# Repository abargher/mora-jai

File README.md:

# Project Mora Jai

A physical Mora Jai puzzle box (from Blue Prince) with programmable RGB LEDs.

Hardware is licensed under the `CERN-OHL-S-2.0` license (e.g., files in`pcb/`).

Code is licensed under the `GPL-3.0-or-later` license.

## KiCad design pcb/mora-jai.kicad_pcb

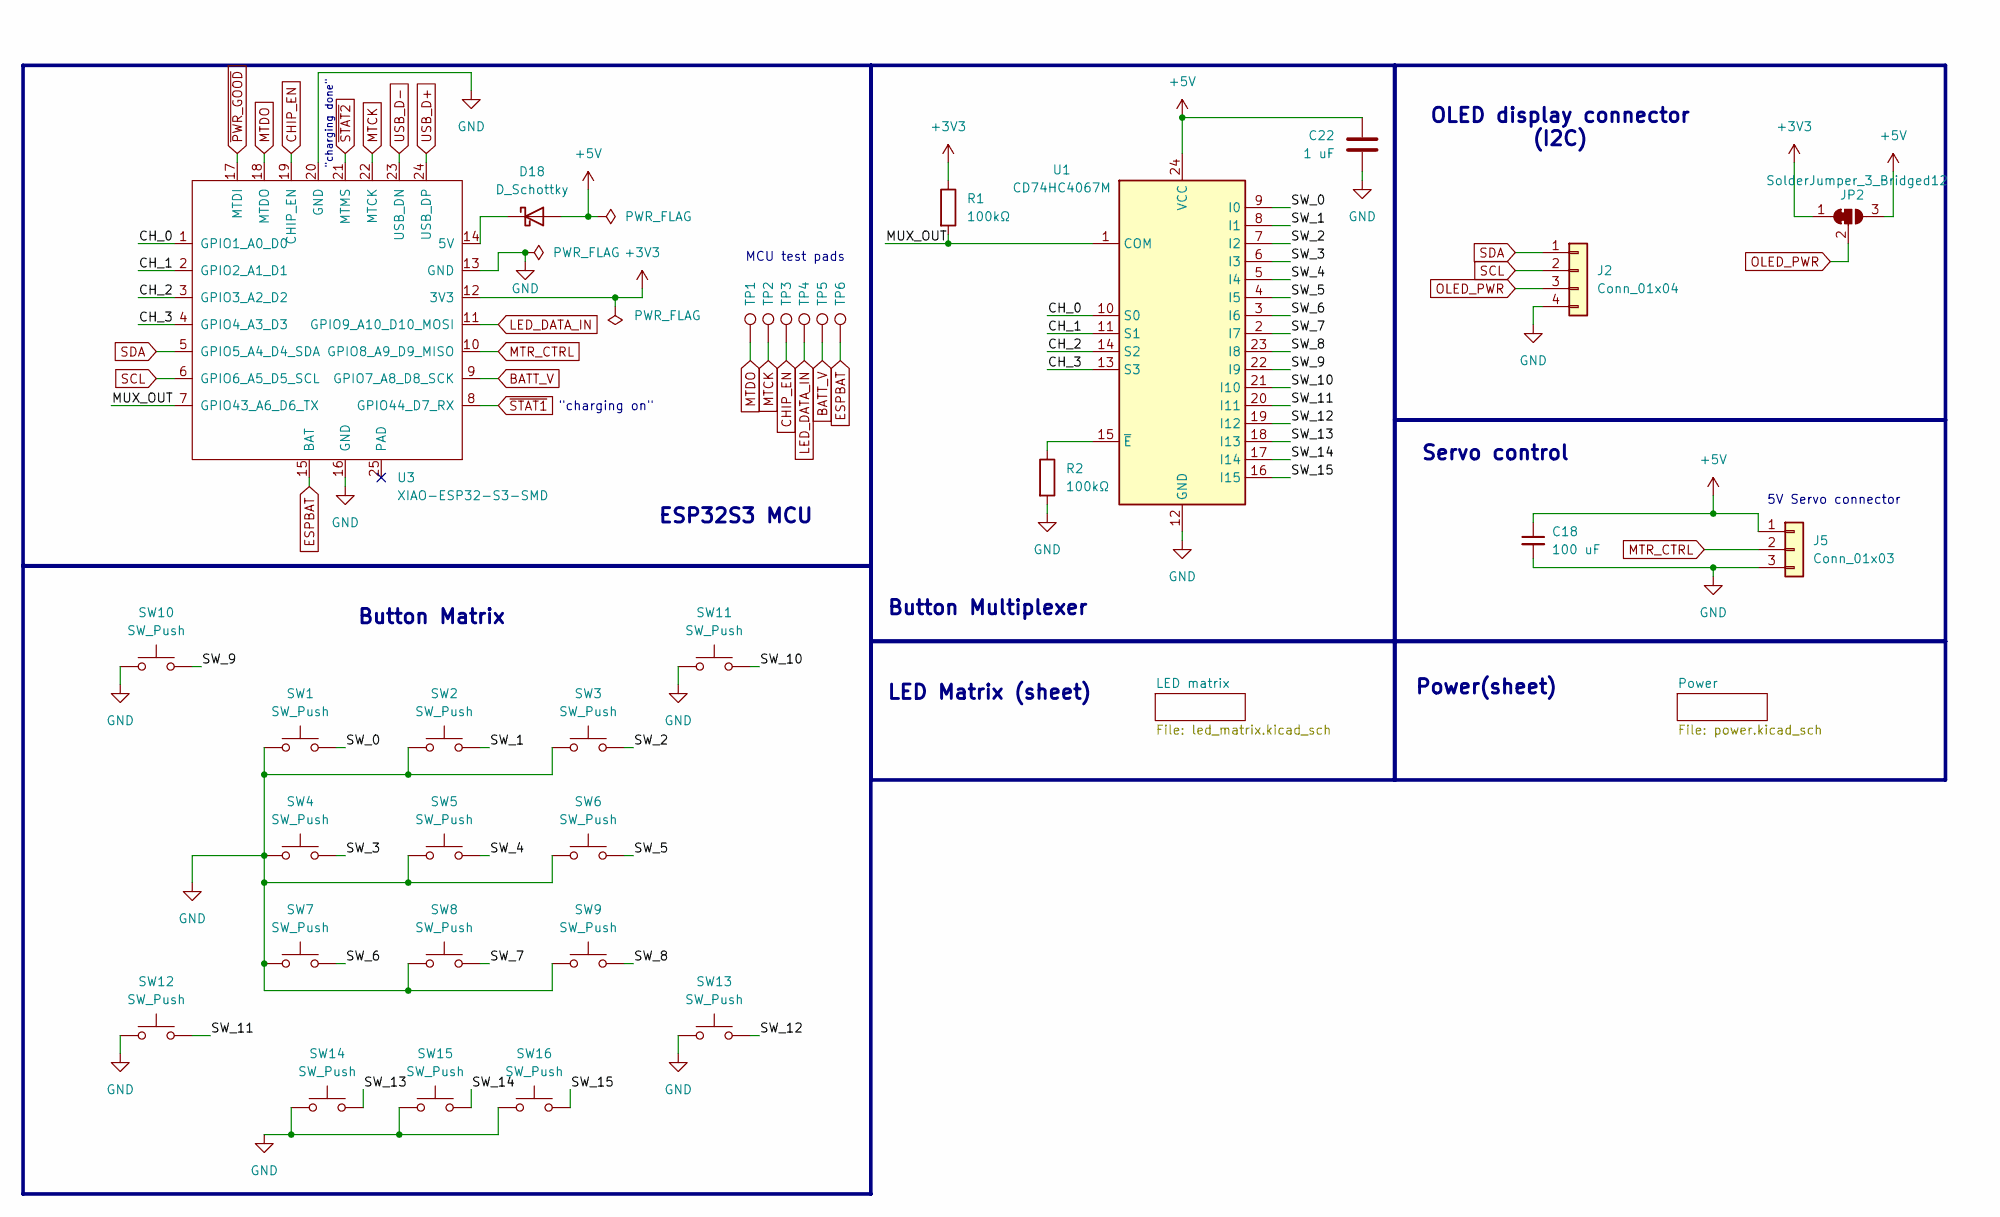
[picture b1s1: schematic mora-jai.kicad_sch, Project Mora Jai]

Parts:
C18: 100 uF; C_0805_2012Metric_Pad1.18x1.45mm_HandSolder
C22: 1 uF; C_0805_2012Metric_Pad1.18x1.45mm_HandSolder
D18: D_Schottky; D_SOD-123F
J2: Conn_01x04; PinSocket_1x04_P2.54mm_Vertical
J5: Conn_01x03; PinHeader_1x03_P2.54mm_Vertical
JP2: SolderJumper_3_Bridged12; SolderJumper-3_P1.3mm_Bridged12_RoundedPad1.0x1.5mm
R1, R2: 100kΩ; R_0805_2012Metric_Pad1.20x1.40mm_HandSolder
SW1, SW2, SW3, SW4, SW5, SW6, SW7, SW8, SW9, SW10, SW11, SW12, SW13, SW14, SW15, SW16: SW_Push; SW_PUSH_6mm_H5mm
TP1, TP2, TP3, TP4, TP5, TP6: TestPoint; TestPoint_Pad_D2.5mm
U1: CD74HC4067M; SOIC-24W_7.5x15.4mm_P1.27mm
U3: XIAO-ESP32-S3-SMD; XIAO-ESP32S3-SMD-batt-tht

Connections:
+3V3: JP2.1 (A), R1.1, U3.12 (3V3); also elsewhere on the board
+5V: C18.1, C22.2, D18.2 (A), J5.1, JP2.3 (B), U1.24 (VCC); also elsewhere on the board
/CH_0: U1.10 (S0), U3.1 (GPIO1_A0_D0)
/CH_1: U1.11 (S1), U3.2 (GPIO2_A1_D1)
/CH_2: U1.14 (S2), U3.3 (GPIO3_A2_D2)
/CH_3: U1.13 (S3), U3.4 (GPIO4_A3_D3)
/MUX_OUT: R1.2, U1.1 (COM), U3.7 (GPIO43_A6_D6_TX)
/SW_0: SW1.2, U1.9 (I0)
/SW_1: SW2.2, U1.8 (I1)
/SW_2: SW3.2, U1.7 (I2)
/SW_3: SW4.2, U1.6 (I3)
/SW_4: SW5.2, U1.5 (I4)
/SW_5: SW6.2, U1.4 (I5)
/SW_6: SW7.2, U1.3 (I6)
/SW_7: SW8.2, U1.2 (I7)
/SW_8: SW9.2, U1.23 (I8)
/SW_9: SW10.2, U1.22 (I9)
/SW_10: SW11.2, U1.21 (I10)
/SW_11: SW12.2, U1.20 (I11)
/SW_12: SW13.2, U1.19 (I12)
/SW_13: SW14.2, U1.18 (I13)
/SW_14: SW15.2, U1.17 (I14)
/SW_15: SW16.2, U1.16 (I15)
BATT_V: TP5.1 (1_1), U3.9 (GPIO7_A8_D8_SCK); also elsewhere on the board
CHIP_EN: TP3.1 (1_1), U3.19 (CHIP_EN)
ESPBAT: TP6.1 (1_1), U3.15 (BAT)
GND: C18.2, C22.1, J2.4, J5.3, R2.2, SW1.1, SW2.1, SW3.1, SW4.1, SW5.1, SW6.1, SW7.1, SW8.1, SW9.1, SW10.1, SW11.1, SW12.1, SW13.1, SW14.1, SW15.1, SW16.1, U1.12 (GND), U3.13 (GND), U3.16 (GND), U3.20 (GND); also elsewhere on the board
LED_DATA_IN: TP4.1 (1_1), U3.11 (GPIO9_A10_D10_MOSI); also elsewhere on the board
MTCK: TP2.1 (1_1), U3.22 (MTCK)
MTDO: TP1.1 (1_1), U3.18 (MTDO)
MTR_CTRL: J5.2, U3.10 (GPIO8_A9_D9_MISO)
unnamed: D18.1 (K), U3.14 (5V)
unnamed: R2.1, U1.15 (~E)
OLED_PWR: J2.3, JP2.2 (C)
SCL: J2.2, U3.6 (GPIO6_A5_D5_SCL)
SDA: J2.1, U3.5 (GPIO5_A4_D4_SDA)
USB_D+: U3.24 (USB_DP); also elsewhere on the board
USB_D-: U3.23 (USB_DN); also elsewhere on the board
~PWR_GOOD: U3.17 (MTDI); also elsewhere on the board
~STAT1: U3.8 (GPIO44_D7_RX); also elsewhere on the board
~STAT2: U3.21 (MTMS); also elsewhere on the board

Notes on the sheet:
Power(sheet)
ESP32S3 MCU
Servo control
"charging on"
"charging done"
MCU test pads
5V Servo connector
Button Matrix
OLED display connector (I2C)
LED Matrix (sheet)
Button Multiplexer

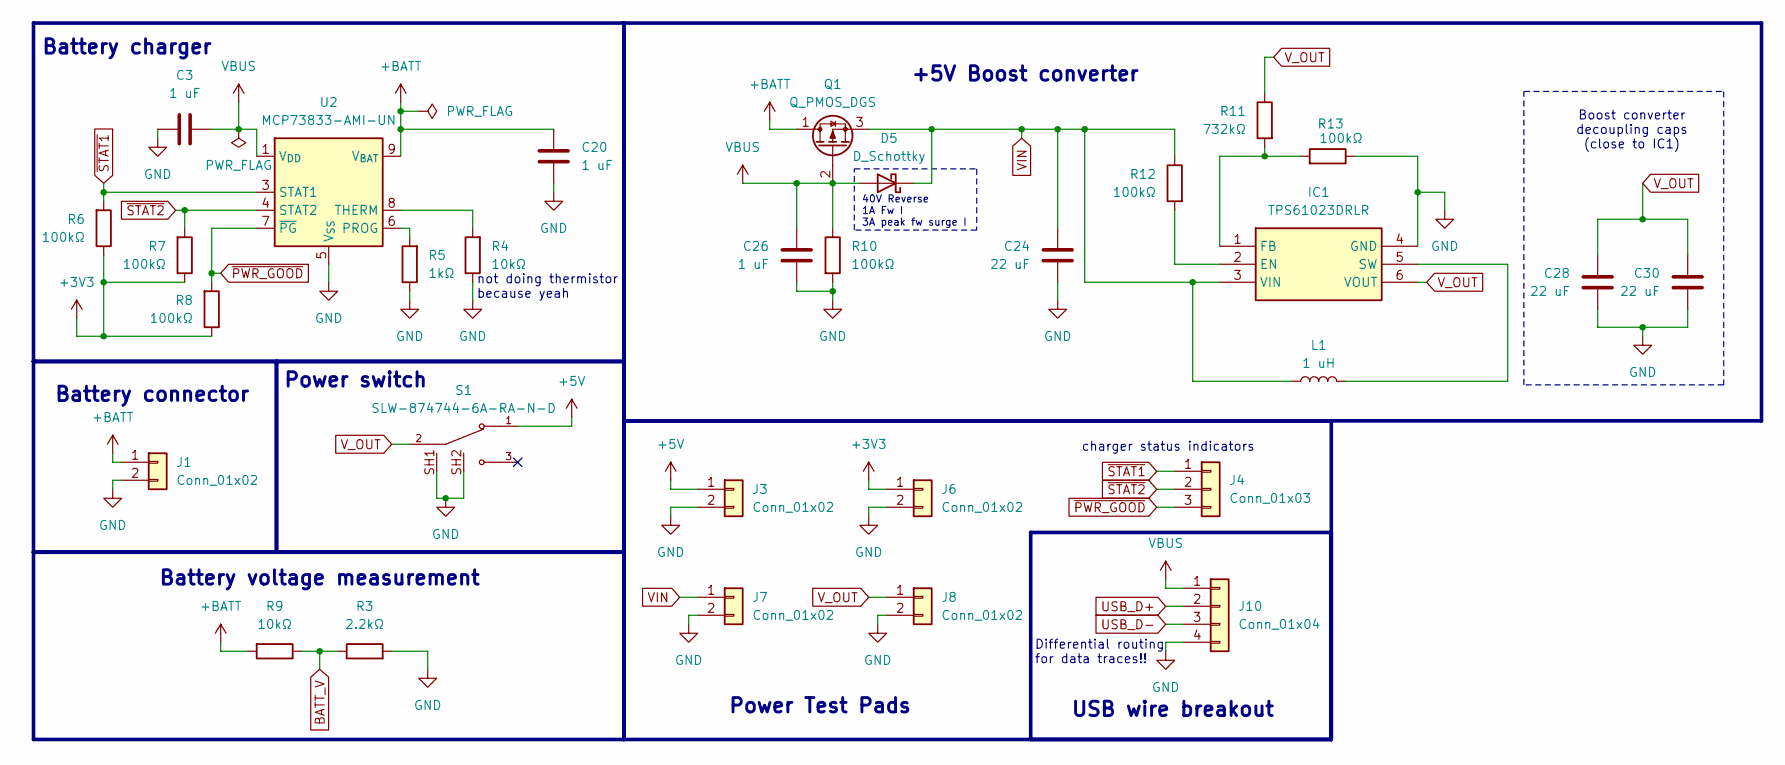
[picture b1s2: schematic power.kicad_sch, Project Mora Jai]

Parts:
C3, C20, C26: 1 uF; C_0805_2012Metric_Pad1.18x1.45mm_HandSolder
C24, C28, C30: 22 uF; C_0805_2012Metric_Pad1.18x1.45mm_HandSolder
D5: D_Schottky; D_SOD-123F
IC1: TPS61023DRLR; SOTFL50P160X60-6N; Mouser Part Number 595-TPS61023DRLR
J1: Conn_01x02; JST_PH_S2B-PH-K_1x02_P2.00mm_Horizontal
J3, J6, J7, J8: Conn_01x02; PinSocket_1x02_P2.54mm_Vertical
J4: Conn_01x03; PinSocket_1x03_P2.54mm_Vertical
J10: Conn_01x04; PinSocket_1x04_P2.54mm_Vertical
L1: 1 uH; 74438356010
Q1: Q_PMOS_DGS; SOT-323_SC-70
R3: 2.2kΩ; R_0805_2012Metric_Pad1.20x1.40mm_HandSolder
R4, R9: 10kΩ; R_0805_2012Metric_Pad1.20x1.40mm_HandSolder
R5: 1kΩ; R_0805_2012Metric_Pad1.20x1.40mm_HandSolder
R6, R7, R8, R10, R12, R13: 100kΩ; R_0805_2012Metric_Pad1.20x1.40mm_HandSolder
R11: 732kΩ; R_0805_2012Metric_Pad1.20x1.40mm_HandSolder
S1: SLW-874744-6A-RA-N-D; SW_SLW-874744-6A-RA-N-D; PARTREV 1.01
U2: MCP73833-AMI-UN; MSOP-10_3x3mm_P0.5mm

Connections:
+3V3: J6.1, R6.1, R7.1, R8.1; also elsewhere on the board
+5V: J3.1, S1.1; also elsewhere on the board
+BATT: C20.1, J1.1, Q1.1 (D), R9.2, U2.9 (V_{BAT}), U2.10 (V_{BAT})
BATT_V: R3.1, R9.1; also elsewhere on the board
GND: C3.1, C20.2, C24.2, C26.2, C28.2, C30.2, IC1.4 (GND), J1.2, J3.2, J6.2, J7.2, J8.2, J10.4, R3.2, R4.1, R5.1, R10.2, R13.1, S1.SH1, S1.SH2, U2.5 (V_{SS}); also elsewhere on the board
unnamed: IC1.2 (EN), R12.2
unnamed: IC1.1 (FB), R11.2, R13.2
unnamed: IC1.5 (SW), L1.2
unnamed: R5.2, U2.6 (PROG)
unnamed: R4.2, U2.8 (THERM)
USB_D+: J10.2; also elsewhere on the board
USB_D-: J10.3; also elsewhere on the board
VBUS: C3.2, C26.1, D5.2 (A), J10.1, Q1.2 (G), R10.1, U2.1 (V_{DD}), U2.2 (V_{DD})
VIN: C24.1, D5.1 (K), IC1.3 (VIN), J7.1, L1.1, Q1.3 (S), R12.1
V_OUT: C28.1, C30.1, IC1.6 (VOUT), J8.1, R11.1, S1.2
~PWR_GOOD: J4.3, R8.2, U2.7 (~PG); also elsewhere on the board
~STAT1: J4.1, R6.2, U2.3 (STAT1); also elsewhere on the board
~STAT2: J4.2, R7.2, U2.4 (STAT2); also elsewhere on the board

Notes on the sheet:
Battery voltage measurement
Battery charger
charger status indicators
Differential routing for data traces!!
Battery connector
USB wire breakout
not doing thermistor because yeah
Boost converter decoupling caps (close to IC1)
40V Reverse 1A Fw I 3A peak fw surge I
Power switch
Power Test Pads
+5V Boost converter

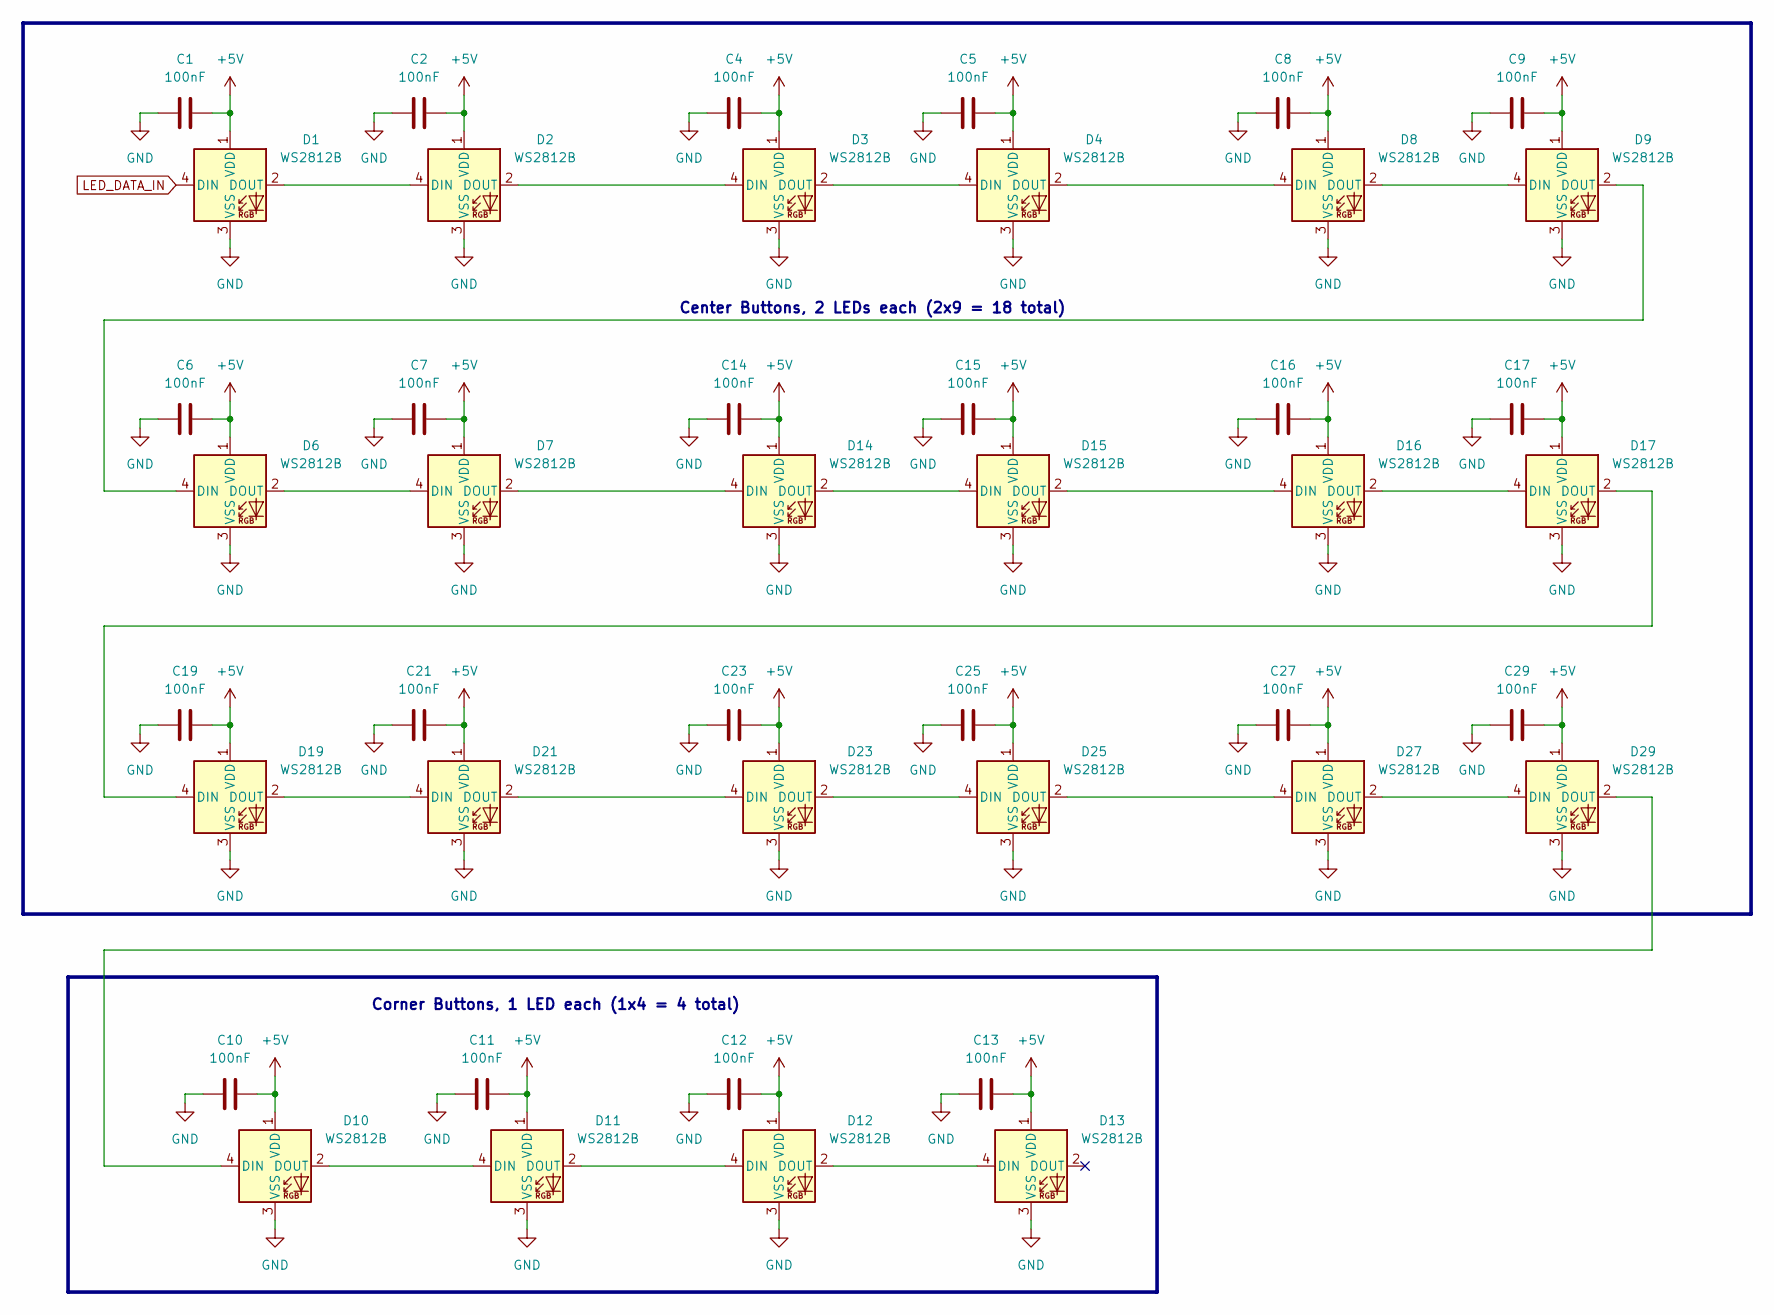
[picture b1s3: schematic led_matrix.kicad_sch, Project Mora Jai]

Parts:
C1, C2, C4, C5, C6, C7, C8, C9, C10, C11, C12, C13, C14, C15, C16, C17, C19, C21, C23, C25, C27, C29: 100nF; C_0805_2012Metric_Pad1.18x1.45mm_HandSolder
D1, D2, D3, D4, D6, D7, D8, D9, D10, D11, D12, D13, D14, D15, D16, D17, D19, D21, D23, D25, D27, D29: WS2812B; LED_WS2812B_PLCC4_5.0x5.0mm_P3.2mm

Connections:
+5V: C1.2, C2.2, C4.2, C5.2, C6.2, C7.2, C8.2, C9.2, C10.2, C11.2, C12.2, C13.2, C14.2, C15.2, C16.2, C17.2, C19.2, C21.2, C23.2, C25.2, C27.2, C29.2, D1.1 (VDD), D2.1 (VDD), D3.1 (VDD), D4.1 (VDD), D6.1 (VDD), D7.1 (VDD), D8.1 (VDD), D9.1 (VDD), D10.1 (VDD), D11.1 (VDD), D12.1 (VDD), D13.1 (VDD), D14.1 (VDD), D15.1 (VDD), D16.1 (VDD), D17.1 (VDD), D19.1 (VDD), D21.1 (VDD), D23.1 (VDD), D25.1 (VDD), D27.1 (VDD), D29.1 (VDD); also elsewhere on the board
GND: C1.1, C2.1, C4.1, C5.1, C6.1, C7.1, C8.1, C9.1, C10.1, C11.1, C12.1, C13.1, C14.1, C15.1, C16.1, C17.1, C19.1, C21.1, C23.1, C25.1, C27.1, C29.1, D1.3 (VSS), D2.3 (VSS), D3.3 (VSS), D4.3 (VSS), D6.3 (VSS), D7.3 (VSS), D8.3 (VSS), D9.3 (VSS), D10.3 (VSS), D11.3 (VSS), D12.3 (VSS), D13.3 (VSS), D14.3 (VSS), D15.3 (VSS), D16.3 (VSS), D17.3 (VSS), D19.3 (VSS), D21.3 (VSS), D23.3 (VSS), D25.3 (VSS), D27.3 (VSS), D29.3 (VSS); also elsewhere on the board
LED_DATA_IN: D1.4 (DIN); also elsewhere on the board
unnamed: D1.2 (DOUT), D2.4 (DIN)
unnamed: D2.2 (DOUT), D3.4 (DIN)
unnamed: D3.2 (DOUT), D4.4 (DIN)
unnamed: D4.2 (DOUT), D8.4 (DIN)
unnamed: D6.4 (DIN), D9.2 (DOUT)
unnamed: D6.2 (DOUT), D7.4 (DIN)
unnamed: D8.2 (DOUT), D9.4 (DIN)
unnamed: D10.4 (DIN), D29.2 (DOUT)
unnamed: D10.2 (DOUT), D11.4 (DIN)
unnamed: D11.2 (DOUT), D12.4 (DIN)
unnamed: D12.2 (DOUT), D13.4 (DIN)
unnamed: D7.2 (DOUT), D14.4 (DIN)
unnamed: D14.2 (DOUT), D15.4 (DIN)
unnamed: D15.2 (DOUT), D16.4 (DIN)
unnamed: D16.2 (DOUT), D17.4 (DIN)
unnamed: D17.2 (DOUT), D19.4 (DIN)
unnamed: D19.2 (DOUT), D21.4 (DIN)
unnamed: D21.2 (DOUT), D23.4 (DIN)
unnamed: D23.2 (DOUT), D25.4 (DIN)
unnamed: D25.2 (DOUT), D27.4 (DIN)
unnamed: D27.2 (DOUT), D29.4 (DIN)

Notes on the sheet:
Corner Buttons, 1 LED each (1x4 = 4 total)
Center Buttons, 2 LEDs each (2x9 = 18 total)

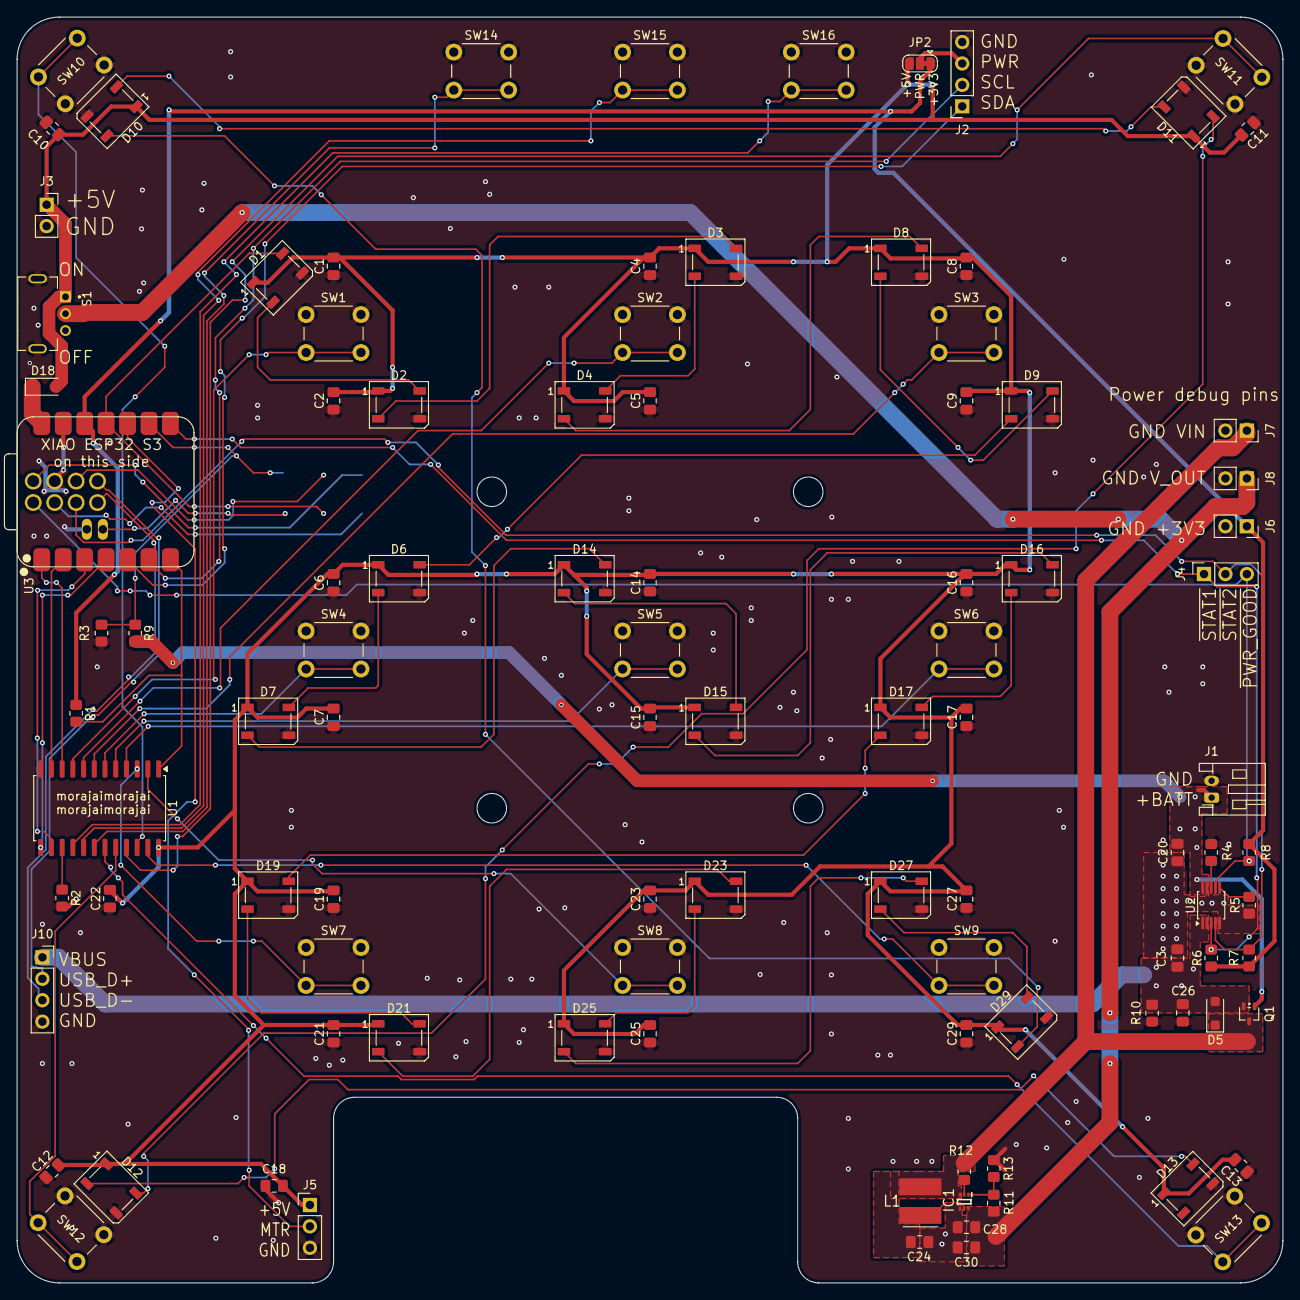
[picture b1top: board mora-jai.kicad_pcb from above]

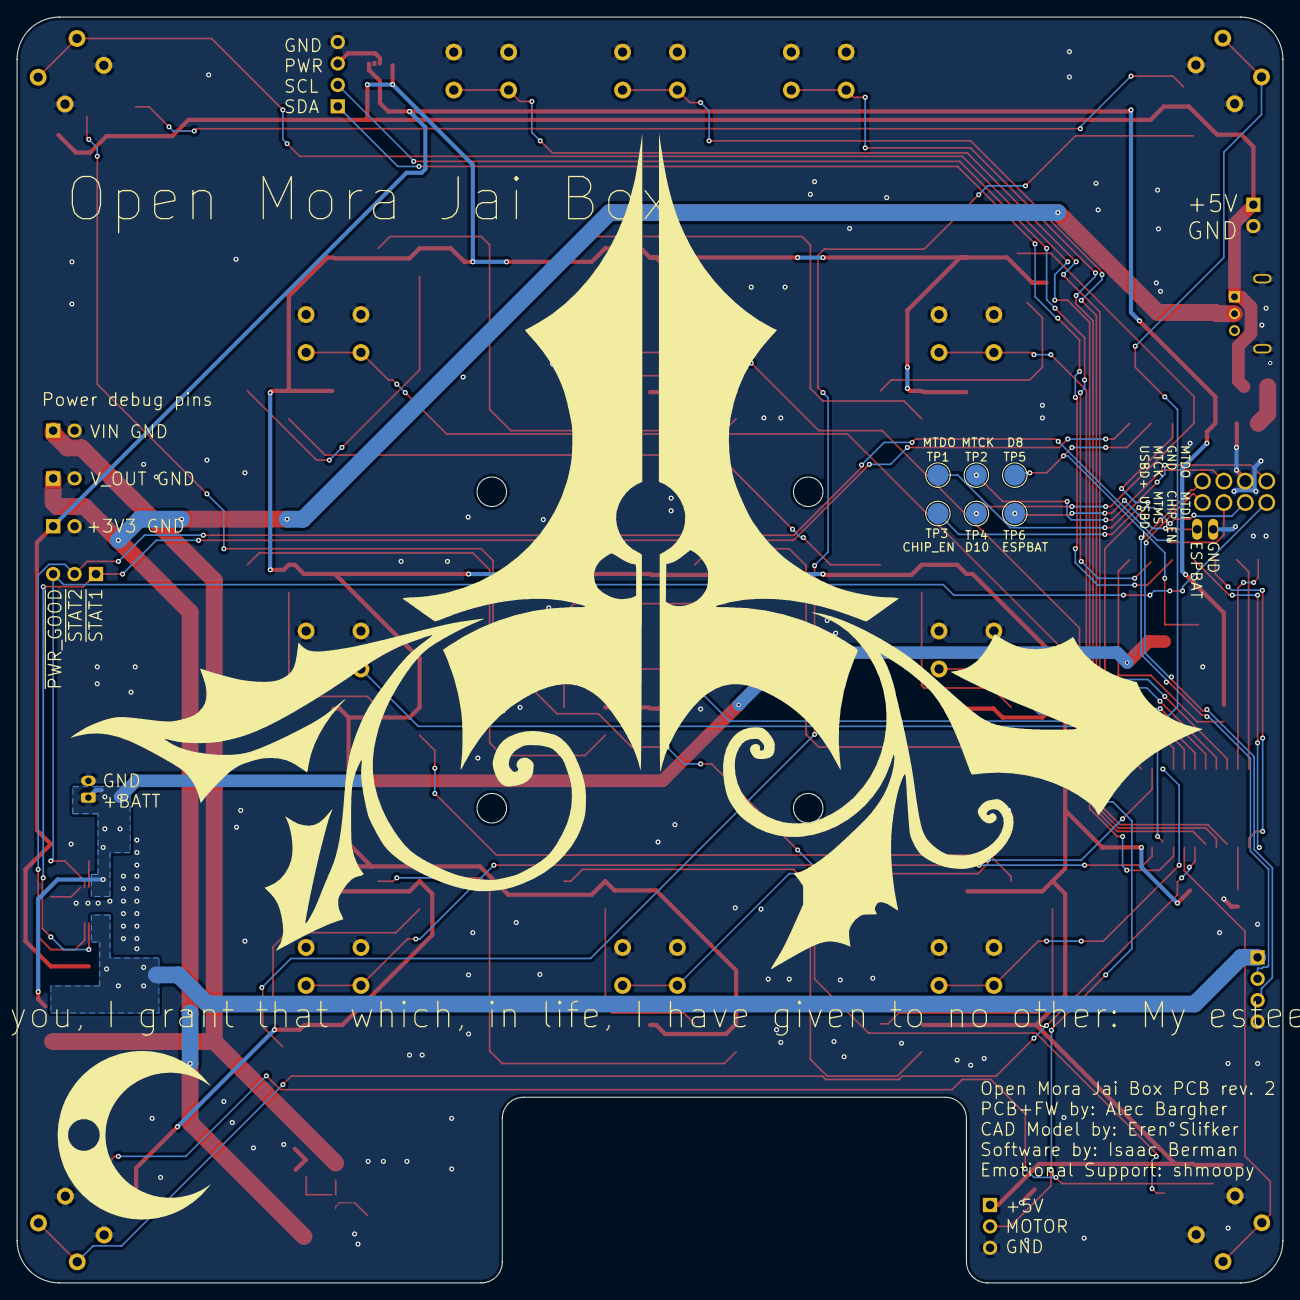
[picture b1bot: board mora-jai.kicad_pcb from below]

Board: 2 copper layers, 150.0 x 150.0 mm, 106 parts (6 on the bottom side), 71 nets.

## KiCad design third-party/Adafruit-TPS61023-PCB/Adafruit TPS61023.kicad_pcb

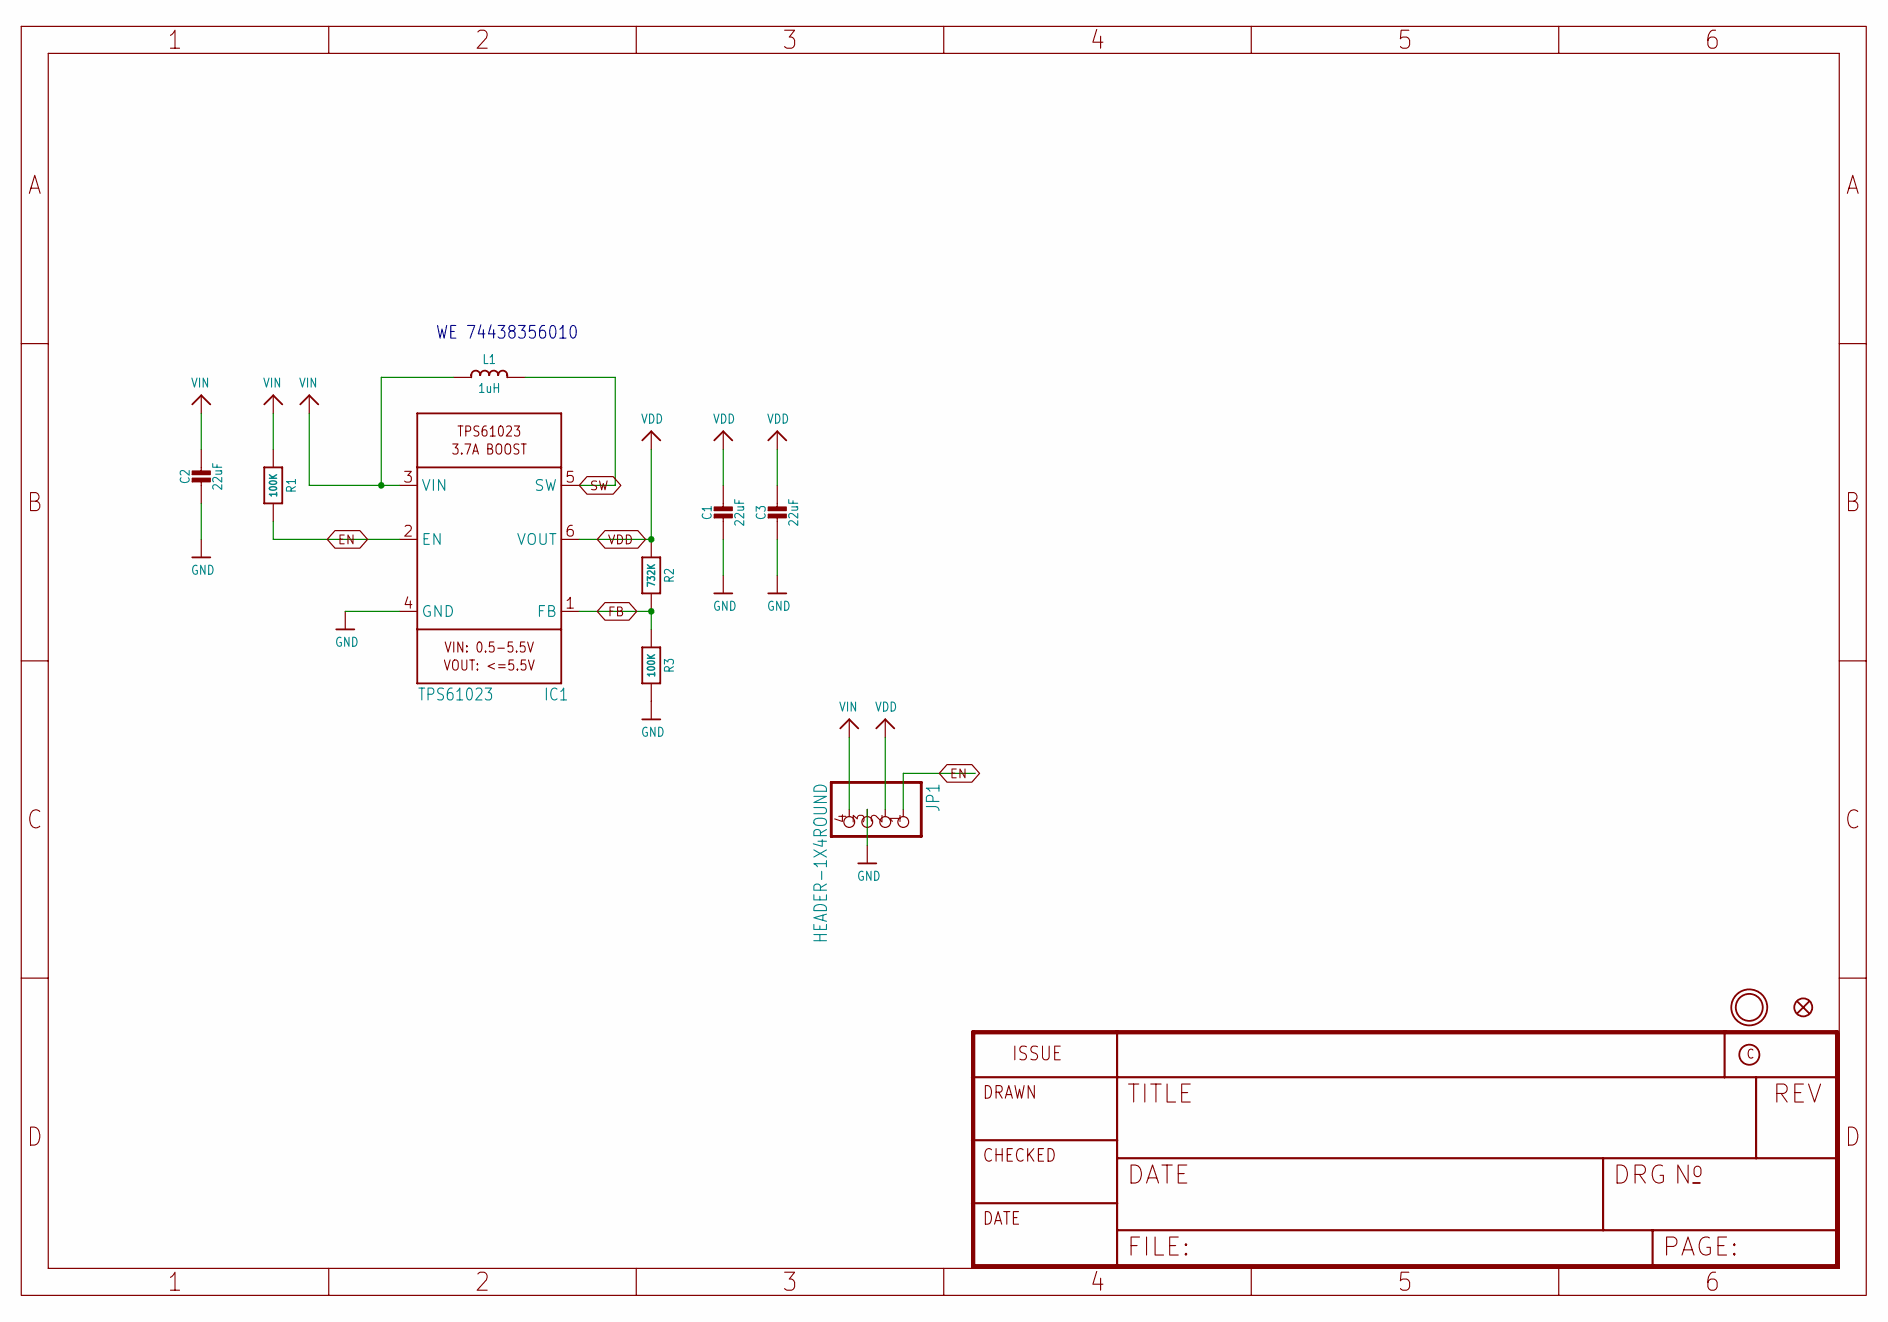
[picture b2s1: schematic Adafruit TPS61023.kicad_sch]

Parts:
C1, C2, C3: 22uF; 0805-NO
FID1: FIDUCIAL_1MM
IC1: TPS61023; SOT563
JP1: HEADER-1X4ROUND; 1X04_ROUND
L1: 1uH; INDUCTOR_5X5MM_TDK_VLC5045
R1, R3: 100K; 0603-NO
R2: 732K; 0603-NO
U$9: MOUNTINGHOLE2.5; MOUNTINGHOLE_2.5_PLATED

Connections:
EN: IC1.2 (EN), JP1.1, R1.2
FB: IC1.1 (FB), R2.2, R3.1
GND: C1.2, C2.2, C3.2, IC1.4 (GND), JP1.3, R3.2
SW: IC1.5 (SW), L1.P$2 (2)
VDD: C1.1, C3.1, IC1.6 (VOUT), JP1.2, R2.1
VIN: C2.1, IC1.3 (VIN), JP1.4, L1.P$1 (1), R1.1

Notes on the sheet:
WE 74438356010

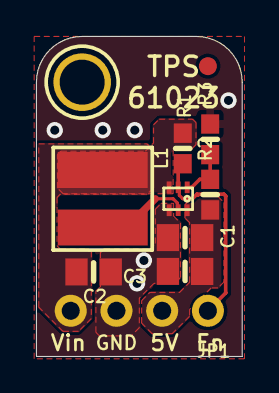
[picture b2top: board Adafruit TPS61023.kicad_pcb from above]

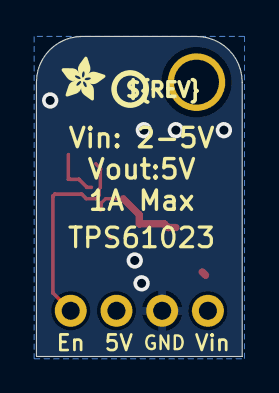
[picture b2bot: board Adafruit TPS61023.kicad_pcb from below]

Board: 2 copper layers, 11.4 x 17.8 mm, 13 parts (2 on the bottom side), 6 nets.

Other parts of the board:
U$10: PCBFEAT-REV-040
U$11: ADAFRUIT_2.5MM

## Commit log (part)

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2026-01-28 initialize kicad project
2026-01-28 some docs
2026-01-29 lay out MCU, buttons, mux, and some initial LEDs in schematic
2026-01-30 move pcb files to directory
2026-01-30 add open source licenses
2026-01-31 reference models and blend file
2026-01-31 add Arduino matrix proof of concept
2026-02-03 Can now read buttons through multiplexer and update LEDs based on button state
2026-02-05 button testing models
2026-02-05 button wall thickness edit
2026-02-05 add PlatformIO project code
2026-02-05 connect all components in schematic, only 13 LEDs for now
2026-02-05 add description to schematic sheets
2026-02-05 more button testing models
2026-02-06 start PCB dimensions
2026-02-07 add a todo for schematic
2026-02-23 some models
2026-02-23 add power switch, more LEDs, and custom symbols/footprints to project
2026-02-23 button sketch
2026-02-23 better sketch?
2026-02-23 main switch layout complete, begin layout of LEDs and capacitors
2026-02-23 cam model progress and pcb mounting sketch
2026-02-23 finish LED and button layout, peripherals next. Update ESP32 footprint battery pads
2026-02-23 remove extraneous line
2026-02-23 relocate MCU and battery connector to proper sides
2026-03-15 power pads
2026-03-16 add question
2026-03-16 proof of concept for solenoid circuit
2026-06-24 motor driver test code
2026-06-24 update motor control circuit in schematic
2026-06-27 add servo control circuit to PCB
